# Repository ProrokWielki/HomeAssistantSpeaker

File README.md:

## HomeAssistantSpeaker

It is a small, 3D printable rhasspy satellite. It uses INMP441 microphone, MAX98357A audio amplifier paired with 8 Ohm 0.5 W broadband speaker, NeoPixel led strip and ESP32. It is powered from 5V USB.

## What you need

Running [Rhasspy](https://rhasspy.readthedocs.io/en/latest/) instance

To build it you will need:
* 3D printed speaker housing  - [stl file](.Mechanics/HomeAssistentSpeaker.stl)
* PCB - [KiCad Project](./Hardware/)
* 8 Ohm 0.5 W 50 mm broadband speaker
* NeoPixel led strip - Optional
* INMP441
* MAX98357A
* ESP32 - module itself
* LM1117-3.3
* USB connector - 6 pin
* a few passive components - resistors and capacitors

And most important **Soldering skills**

## Assambly

* Solder everything together

* Put it inside the shell (order from the bottom: speaker, board, led strip)

* Add speaker mesh fabric

## Demo

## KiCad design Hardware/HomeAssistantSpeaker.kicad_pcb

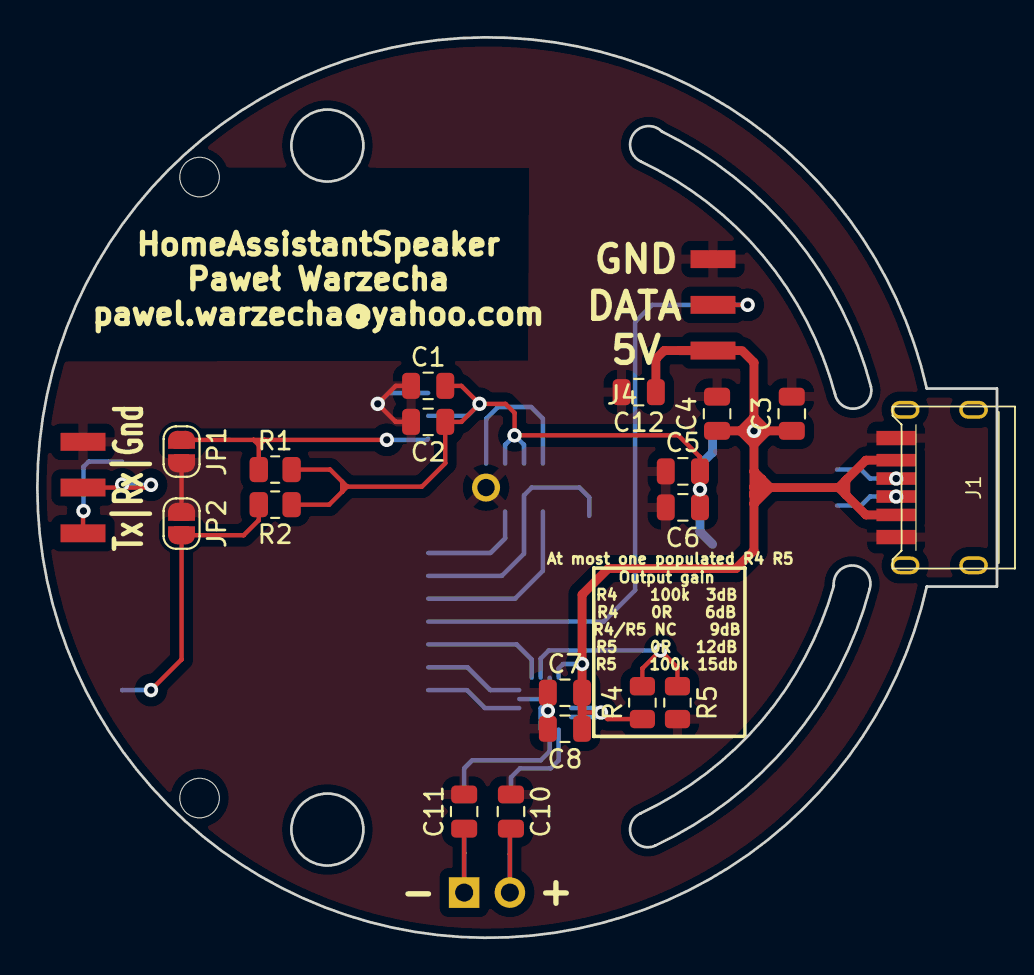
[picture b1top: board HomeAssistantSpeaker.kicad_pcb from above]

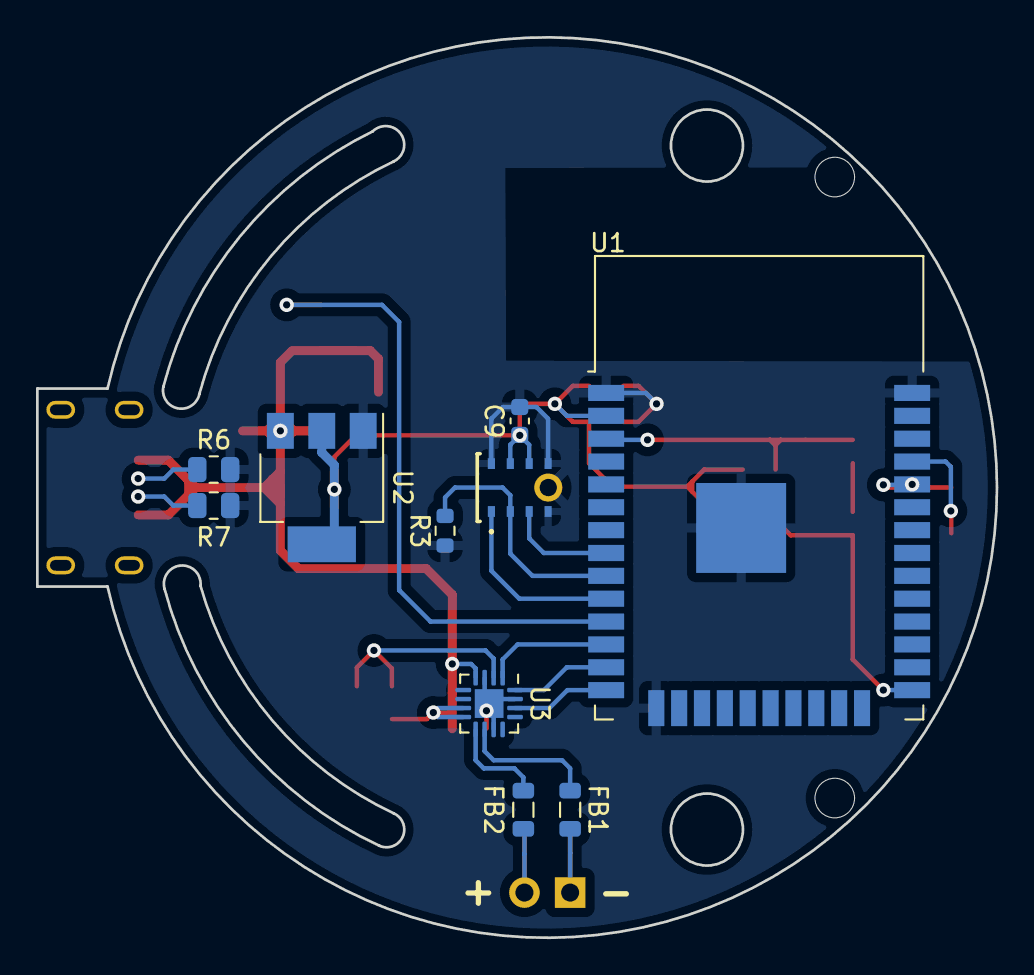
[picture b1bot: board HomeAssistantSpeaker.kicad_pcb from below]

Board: 2 copper layers, 53.3 x 50.0 mm, 31 parts (10 on the bottom side), 21 nets.

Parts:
C1, C3, C5, C7: 100n; C_0805_2012Metric
C2, C4, C6, C8: 10u; C_0805_2012Metric
C9: 100n; C_0603_1608Metric
C10, C11: 220p; C_0805_2012Metric
C12: 1u; C_0805_2012Metric
FB1, FB2: 20uH; L_0805_2012Metric
J1: USB_C_Receptacle_USB2.0; TYPE-C-31-M-17_handsolder
J2: Speaker; PinHeader_1x02_P2.54mm_Vertical
J3: Prog; Harwin_M20-89003xx_1x03_P2.54mm_Horizontal
J4: LED; Harwin_M20-89003xx_1x03_P2.54mm_Horizontal
JP1: Reset; SolderJumper-2_P1.3mm_Open_RoundedPad1.0x1.5mm
JP2: Program; SolderJumper-2_P1.3mm_Open_RoundedPad1.0x1.5mm
MK1: INMP441ACEZ
R1, R2, R4, R5: 10k; R_0805_2012Metric
R3: 100k; R_0603_1608Metric
R6, R7: 5k1; R_0805_2012Metric
U1: ESP32-WROOM-32
U2: LM1117-3.3; SOT-223-3_TabPin2
U3: MAX98357AETE+; TQFN-16-1EP_3x3mm_P0.5mm_EP1.6x1.6mm

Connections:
+3V3: C1.1, C2.1, C5.1, C6.1, C9.1, MK1.7 (VDD), MK1.8 (CHIPEN), R1.1, R2.1, U1.2 (VDD), U2.2 (VO)
+5V: C3.1, C4.1, C7.1, C8.1, C12.1, J1.A9 (VBUS), J1.B9 (VBUS), J4.1, R4.1, U2.3 (VI), U3.4 (~SD_MODE), U3.7 (VDD), U3.8 (VDD)
GND: C1.2, C2.2, C3.2, C4.2, C5.2, C6.2, C7.2, C8.2, C9.2, C10.2, C11.2, C12.2, J1.A12 (GND), J1.B12 (GND), J3.3, J4.3, JP1.1, JP2.2, MK1.4 (L/R), MK1.5 (GND_1), MK1.6 (GND_2), MK1.9 (GND_3), R3.2, R5.1, R6.2, R7.2, U1.1 (GND), U1.15 (GND), U1.38 (GND), U1.39 (GND), U2.1 (GND), U3.3 (GND), U3.11 (GND), U3.15 (GND), U3.17 (EP)
Gain: R4.2, R5.2, U3.2 (GAIN_SLOT)
LED_DATA: J4.2, U1.11 (IO26)
Mic_SCK: MK1.1 (SCK), U1.10 (IO25)
Mic_SD: MK1.2 (SD), R3.1, U1.9 (IO33)
Mic_WS: MK1.3 (WS), U1.8 (IO32)
unnamed: C10.1, FB2.1, J2.2
unnamed: C11.1, FB1.1, J2.1
unnamed: FB1.2, U3.10 (OUTN)
unnamed: FB2.2, U3.9 (OUTP)
unnamed: J1.A5 (CC1), R7.1
unnamed: J1.B5 (CC2), R6.1
unnamed: JP1.2, R1.2, U1.3 (EN)
unnamed: JP2.1, R2.2, U1.25 (IO0)
Rx: J3.2, U1.34 (RXD0/IO3)
Speaker_bclk: U1.13 (IO14), U3.16 (BCLK)
Speaker_din: U1.12 (IO27), U3.1 (DIN)
Speaker_lrclk: U1.14 (IO12), U3.14 (LRCLK)
Tx: J3.1, U1.35 (TXD0/IO1)

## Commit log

2022-11-20 Inital design of the PCB
2022-12-10 Silkscreen cleanup
    * Moved overlaping silkscreen values
    * Added gain setting info on the PCB
2022-12-12 Converted to KiCad 6
2022-12-12 Added STL and fusion360 files for speaker housing
2022-12-12 Added sumbmodule with software
2022-12-13 Addded readme and needed files
2022-12-29 Rev B:
    * Added missing resitiors for usb c power
2023-01-14 Changed RhasspySatelite submodule to orignal repo
